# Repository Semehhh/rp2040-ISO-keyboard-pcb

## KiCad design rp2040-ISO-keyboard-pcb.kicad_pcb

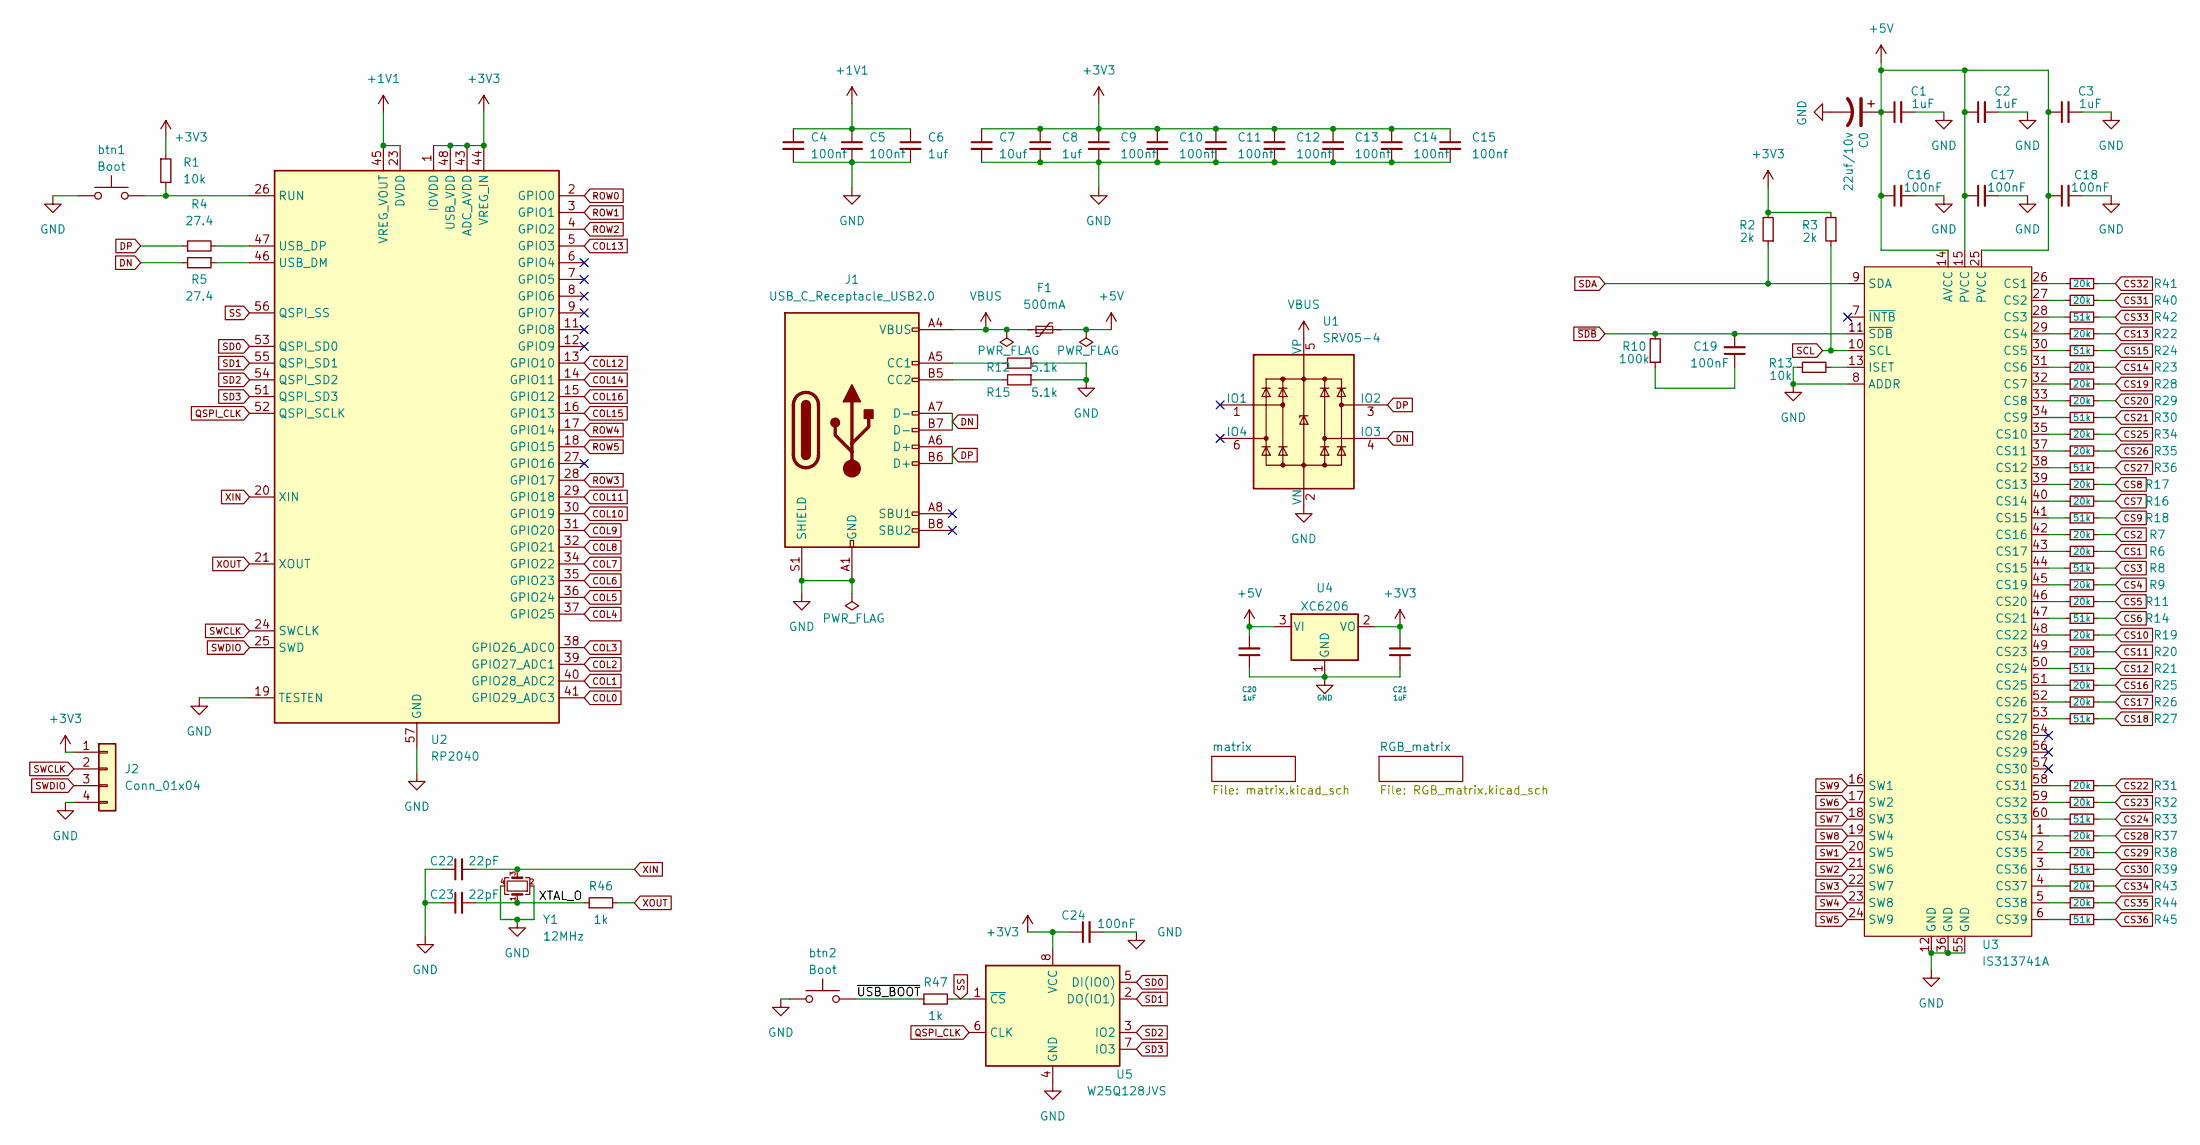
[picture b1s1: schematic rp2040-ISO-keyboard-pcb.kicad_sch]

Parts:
C0: 22uf/10v; CP_EIA-3216-18_Kemet-A; Part Number TAJA226K010RNJ; LCSC C11366
C1, C2, C3: 1uF; C_0402_1005Metric; LCSC C1555
C4, C5, C9, C10, C11, C12, C13, C14, C15: 100nf; C_0402_1005Metric
C6, C8: 1uf; C_0402_1005Metric
C7: 10uf; C_0402_1005Metric
C16, C17, C18, C19: 100nF; C_0402_1005Metric; LCSC C1555
C20, C21: 1uF; C_0402_1005Metric; LCSC C52923
C22, C23: 22pF; C_0402_1005Metric; LCSC C1555
C24: 100nF; C_0402_1005Metric; LCSC C1525
F1: 500mA; Fuse_1206_3216Metric
J1: USB_C_Receptacle_USB2.0; USB_C_Receptacle_HRO_TYPE-C-31-M-14
J2: Conn_01x04; PinHeader_1x04_P2.54mm_Vertical
R1: 10k; R_0402_1005Metric; LCSC C25744
R2, R3: 2k; R_0402_1005Metric
R4, R5: 27.4; R_0603_1608Metric
R6, R7, R9, R11, R16, R17, R19, R20, R22, R23, R25, R26, R28, R29, R31, R32, R34, R35, R37, R38, R40, R41, R43, R44: 20k; R_0402_1005Metric
R8, R14, R18, R21, R24, R27, R30, R33, R36, R39, R42, R45: 51k; R_0402_1005Metric
R10: 100k; R_0402_1005Metric
R12, R15: 5.1k; R_0402_1005Metric
R13: 10k; R_0402_1005Metric
R46, R47: 1k; R_0402_1005Metric; LCSC C11702
U1: SRV05-4; SOT-23-6-routable
U2: RP2040; QFN-56-1EP_7x7mm_P0.4mm_EP3.2x3.2mm
U3: IS313741A; QFN-60_EP_7x7_Pitch0.4mm
U4: XC6206; SOT-23; LCSC C5446
U5: W25Q128JVS; SOIC-8_5.23x5.23mm_P1.27mm; LCSC C97521
Y1: 12MHz; Crystal_SMD_3225-4Pin_3.2x2.5mm; LCSC C9002
btn1, btn2: Boot; PinSocket_1x02_P2.54mm_Vertical

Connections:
+1V1: C4.1, C5.1, C6.1, U2.23 (DVDD), U2.45 (VREG_VOUT), U2.50 (DVDD)
+3V3: C7.1, C8.1, C9.1, C10.1, C11.1, C12.1, C13.1, C14.1, C15.1, C21.2, C24.1, J2.1, R1.1, R2.2, R3.2, U2.1 (IOVDD), U2.10 (IOVDD), U2.22 (IOVDD), U2.33 (IOVDD), U2.42 (IOVDD), U2.43 (ADC_AVDD), U2.44 (VREG_IN), U2.48 (USB_VDD), U2.49 (IOVDD), U4.2 (VO), U5.8 (VCC)
+5V: C0.1, C1.1, C2.1, C3.1, C16.1, C17.1, C18.1, C20.2, F1.2, U3.14 (AVCC), U3.15 (PVCC), U3.25 (PVCC), U4.3 (VI)
/XTAL_O: C23.2, R46.1, Y1.1
/~USB_BOOT: R47.1, btn2.2
COL0: U2.41 (GPIO29_ADC3); also elsewhere on the board
COL1: U2.40 (GPIO28_ADC2); also elsewhere on the board
COL2: U2.39 (GPIO27_ADC1); also elsewhere on the board
COL3: U2.38 (GPIO26_ADC0); also elsewhere on the board
COL4: U2.37 (GPIO25); also elsewhere on the board
COL5: U2.36 (GPIO24); also elsewhere on the board
COL6: U2.35 (GPIO23); also elsewhere on the board
COL7: U2.34 (GPIO22); also elsewhere on the board
COL8: U2.32 (GPIO21); also elsewhere on the board
COL9: U2.31 (GPIO20); also elsewhere on the board
COL10: U2.30 (GPIO19); also elsewhere on the board
COL11: U2.29 (GPIO18); also elsewhere on the board
COL12: U2.13 (GPIO10); also elsewhere on the board
COL13: U2.5 (GPIO3); also elsewhere on the board
COL14: U2.14 (GPIO11); also elsewhere on the board
COL15: U2.16 (GPIO13); also elsewhere on the board
COL16: U2.15 (GPIO12); also elsewhere on the board
CS1: R6.2; also elsewhere on the board
CS2: R7.2; also elsewhere on the board
CS3: R8.2; also elsewhere on the board
CS4: R9.2; also elsewhere on the board
CS5: R11.2; also elsewhere on the board
CS6: R14.2; also elsewhere on the board
CS7: R16.2; also elsewhere on the board
CS8: R17.2; also elsewhere on the board
CS9: R18.2; also elsewhere on the board
CS10: R19.2; also elsewhere on the board
CS11: R20.2; also elsewhere on the board
CS12: R21.2; also elsewhere on the board
CS13: R22.2; also elsewhere on the board
CS14: R23.2; also elsewhere on the board
CS15: R24.2; also elsewhere on the board
CS16: R25.2; also elsewhere on the board
CS17: R26.2; also elsewhere on the board
CS18: R27.2; also elsewhere on the board
CS19: R28.2; also elsewhere on the board
CS20: R29.2; also elsewhere on the board
CS21: R30.2; also elsewhere on the board
CS22: R31.2; also elsewhere on the board
CS23: R32.2; also elsewhere on the board
CS24: R33.2; also elsewhere on the board
CS25: R34.2; also elsewhere on the board
CS26: R35.2; also elsewhere on the board
CS27: R36.2; also elsewhere on the board
CS28: R37.2; also elsewhere on the board
CS29: R38.2; also elsewhere on the board
CS30: R39.2; also elsewhere on the board
CS31: R40.2; also elsewhere on the board
CS32: R41.2; also elsewhere on the board
CS33: R42.2; also elsewhere on the board
CS34: R43.2; also elsewhere on the board
CS35: R44.2; also elsewhere on the board
CS36: R45.2; also elsewhere on the board
DN: J1.A7 (D-), J1.B7 (D-), R5.2, U1.4 (IO3)
DP: J1.A6 (D+), J1.B6 (D+), R4.1, U1.3 (IO2)
GND: C0.2, C1.2, C2.2, C3.2, C4.2, C5.2, C6.2, C7.2, C8.2, C9.2, C10.2, C11.2, C12.2, C13.2, C14.2, C15.2, C16.2, C17.2, C18.2, C20.1, C21.1, C22.1, C23.1, C24.2, J1.A1 (GND), J1.A12 (GND), J1.B1 (GND), J1.B12 (GND), J1.S1 (SHIELD), J2.4, R12.2, R13.1, R15.1, U1.2 (VN), U2.19 (TESTEN), U2.57 (GND), U3.8 (ADDR), U3.12 (GND), U3.36 (GND), U3.55 (GND), U3.61 (GND), U4.1 (GND), U5.4 (GND), Y1.2, Y1.4, btn1.1, btn2.1
unnamed: C19.1, R10.1
unnamed: J1.A5 (CC1), R12.1
unnamed: J1.B5 (CC2), R15.2
unnamed: R1.2, U2.26 (RUN), btn1.2
unnamed: R4.2, U2.47 (USB_DP)
unnamed: R5.1, U2.46 (USB_DM)
unnamed: R6.1, U3.43 (CS17)
unnamed: R7.1, U3.42 (CS16)
unnamed: R8.1, U3.44 (CS15)
unnamed: R9.1, U3.45 (CS19)
unnamed: R13.2, U3.13 (ISET)
unnamed: R16.1, U3.40 (CS14)
unnamed: R17.1, U3.39 (CS13)
unnamed: R18.1, U3.41 (CS15)
unnamed: R19.1, U3.48 (CS22)
unnamed: R20.1, U3.49 (CS23)
unnamed: R21.1, U3.50 (CS24)
unnamed: R22.1, U3.29 (CS4)
unnamed: R23.1, U3.31 (CS6)
unnamed: R24.1, U3.30 (CS5)
unnamed: R25.1, U3.51 (CS25)
unnamed: R26.1, U3.52 (CS26)
unnamed: R27.1, U3.53 (CS27)
unnamed: R28.1, U3.32 (CS7)
unnamed: R29.1, U3.33 (CS8)
unnamed: R30.1, U3.34 (CS9)
unnamed: R31.1, U3.58 (CS31)
unnamed: R32.1, U3.59 (CS32)
unnamed: R33.1, U3.60 (CS33)
unnamed: R34.1, U3.35 (CS10)
unnamed: R35.1, U3.37 (CS11)
unnamed: R36.1, U3.38 (CS12)
unnamed: R37.1, U3.1 (CS34)
unnamed: R38.1, U3.2 (CS35)
unnamed: R39.1, U3.3 (CS36)
unnamed: R40.1, U3.27 (CS2)
unnamed: R41.1, U3.26 (CS1)
unnamed: R42.1, U3.28 (CS3)
unnamed: R43.1, U3.4 (CS37)
unnamed: R44.1, U3.5 (CS38)
unnamed: R45.1, U3.6 (CS39)
unnamed: R11.1, U3.46 (CS20)
unnamed: R14.1, U3.47 (CS21)
QSPI_CLK: U2.52 (QSPI_SCLK), U5.6 (CLK)
ROW0: U2.2 (GPIO0); also elsewhere on the board
ROW1: U2.3 (GPIO1); also elsewhere on the board
ROW2: U2.4 (GPIO2); also elsewhere on the board
ROW3: U2.28 (GPIO17); also elsewhere on the board
ROW4: U2.17 (GPIO14); also elsewhere on the board
ROW5: U2.18 (GPIO15); also elsewhere on the board
SCL: R3.1, U3.10 (SCL)
SD0: U2.53 (QSPI_SD0), U5.5 (DI(IO0))
SD1: U2.55 (QSPI_SD1), U5.2 (DO(IO1))
SD2: U2.54 (QSPI_SD2), U5.3 (IO2)
SD3: U2.51 (QSPI_SD3), U5.7 (IO3)
SDA: R2.1, U3.9 (SDA)
SS: R47.2, U2.56 (QSPI_SS), U5.1 (~CS)
SW1: U3.20 (SW5); also elsewhere on the board
SW2: U3.21 (SW6); also elsewhere on the board
SW3: U3.22 (SW7); also elsewhere on the board
SW4: U3.23 (SW8); also elsewhere on the board
SW5: U3.24 (SW9); also elsewhere on the board
SW6: U3.17 (SW2); also elsewhere on the board
SW7: U3.18 (SW3); also elsewhere on the board
SW8: U3.19 (SW4); also elsewhere on the board
SW9: U3.16 (SW1); also elsewhere on the board
SWCLK: J2.2, U2.24 (SWCLK)
SWDIO: J2.3, U2.25 (SWD)
VBUS: F1.1, J1.A4 (VBUS), J1.A9 (VBUS), J1.B4 (VBUS), J1.B9 (VBUS), U1.5 (VP)
XIN: C22.2, U2.20 (XIN), Y1.3
XOUT: R46.2, U2.21 (XOUT)
~SDB: C19.2, R10.2, U3.11 (~SDB)

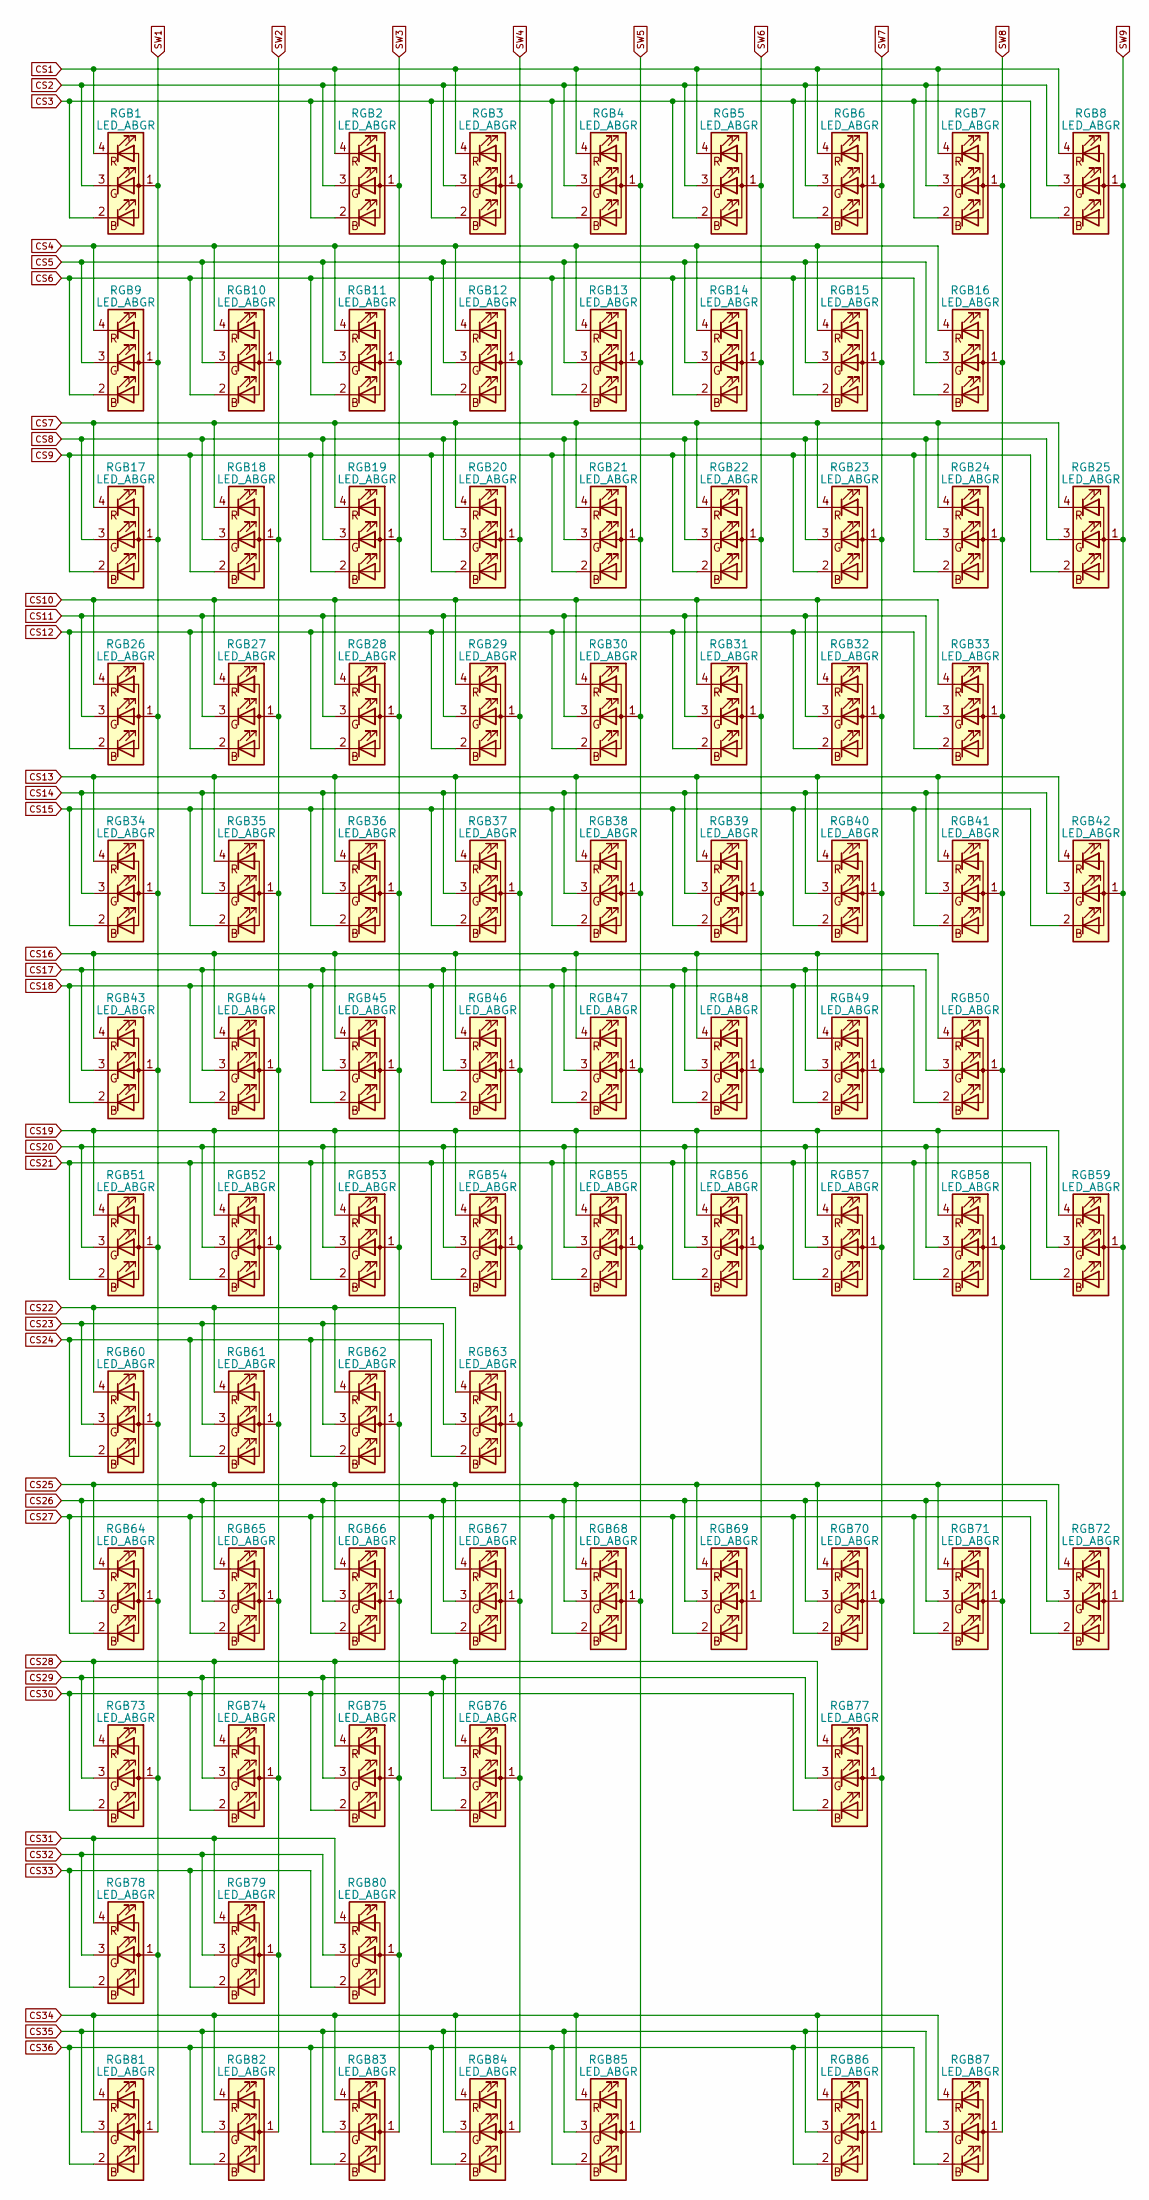
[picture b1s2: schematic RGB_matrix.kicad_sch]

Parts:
RGB1, RGB2, RGB3, RGB4, RGB5, RGB6, RGB7, RGB8, RGB9, RGB10, RGB11, RGB12, RGB13, RGB14, RGB15, RGB16, RGB17, RGB18, RGB19, RGB20, RGB21, RGB22, RGB23, RGB24, RGB25, RGB26, RGB27, RGB28, RGB29, RGB30, RGB31, RGB32, RGB33, RGB34, RGB35, RGB36, RGB37, RGB38, RGB39, RGB40, RGB41, RGB42, RGB43, RGB44, RGB45, RGB46, RGB47, RGB48, RGB49, RGB50, RGB51, RGB52, RGB53, RGB54, RGB55, RGB56, RGB57, RGB58, RGB59, RGB60, RGB61, RGB62, RGB63, RGB64, RGB65, RGB66, RGB67, RGB68, RGB69, RGB70, RGB71, RGB72, RGB73, RGB74, RGB75, RGB76, RGB77, RGB78, RGB79, RGB80, RGB81, RGB82, RGB83, RGB84, RGB85, RGB86, RGB87: LED_ABGR; MHT151RGBCT-RGB-Reverse-Mount-1206

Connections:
CS1: RGB1.4 (RK), RGB2.4 (RK), RGB3.4 (RK), RGB4.4 (RK), RGB5.4 (RK), RGB6.4 (RK), RGB7.4 (RK), RGB8.4 (RK); also elsewhere on the board
CS2: RGB1.3 (GK), RGB2.3 (GK), RGB3.3 (GK), RGB4.3 (GK), RGB5.3 (GK), RGB6.3 (GK), RGB7.3 (GK), RGB8.3 (GK); also elsewhere on the board
CS3: RGB1.2 (BK), RGB2.2 (BK), RGB3.2 (BK), RGB4.2 (BK), RGB5.2 (BK), RGB6.2 (BK), RGB7.2 (BK), RGB8.2 (BK); also elsewhere on the board
CS4: RGB9.4 (RK), RGB10.4 (RK), RGB11.4 (RK), RGB12.4 (RK), RGB13.4 (RK), RGB14.4 (RK), RGB15.4 (RK), RGB16.4 (RK); also elsewhere on the board
CS5: RGB9.3 (GK), RGB10.3 (GK), RGB11.3 (GK), RGB12.3 (GK), RGB13.3 (GK), RGB14.3 (GK), RGB15.3 (GK), RGB16.3 (GK); also elsewhere on the board
CS6: RGB9.2 (BK), RGB10.2 (BK), RGB11.2 (BK), RGB12.2 (BK), RGB13.2 (BK), RGB14.2 (BK), RGB15.2 (BK), RGB16.2 (BK); also elsewhere on the board
CS7: RGB17.4 (RK), RGB18.4 (RK), RGB19.4 (RK), RGB20.4 (RK), RGB21.4 (RK), RGB22.4 (RK), RGB23.4 (RK), RGB24.4 (RK), RGB25.4 (RK); also elsewhere on the board
CS8: RGB17.3 (GK), RGB18.3 (GK), RGB19.3 (GK), RGB20.3 (GK), RGB21.3 (GK), RGB22.3 (GK), RGB23.3 (GK), RGB24.3 (GK), RGB25.3 (GK); also elsewhere on the board
CS9: RGB17.2 (BK), RGB18.2 (BK), RGB19.2 (BK), RGB20.2 (BK), RGB21.2 (BK), RGB22.2 (BK), RGB23.2 (BK), RGB24.2 (BK), RGB25.2 (BK); also elsewhere on the board
CS10: RGB26.4 (RK), RGB27.4 (RK), RGB28.4 (RK), RGB29.4 (RK), RGB30.4 (RK), RGB31.4 (RK), RGB32.4 (RK), RGB33.4 (RK); also elsewhere on the board
CS11: RGB26.3 (GK), RGB27.3 (GK), RGB28.3 (GK), RGB29.3 (GK), RGB30.3 (GK), RGB31.3 (GK), RGB32.3 (GK), RGB33.3 (GK); also elsewhere on the board
CS12: RGB26.2 (BK), RGB27.2 (BK), RGB28.2 (BK), RGB29.2 (BK), RGB30.2 (BK), RGB31.2 (BK), RGB32.2 (BK), RGB33.2 (BK); also elsewhere on the board
CS13: RGB34.4 (RK), RGB35.4 (RK), RGB36.4 (RK), RGB37.4 (RK), RGB38.4 (RK), RGB39.4 (RK), RGB40.4 (RK), RGB41.4 (RK), RGB42.4 (RK); also elsewhere on the board
CS14: RGB34.3 (GK), RGB35.3 (GK), RGB36.3 (GK), RGB37.3 (GK), RGB38.3 (GK), RGB39.3 (GK), RGB40.3 (GK), RGB41.3 (GK), RGB42.3 (GK); also elsewhere on the board
CS15: RGB34.2 (BK), RGB35.2 (BK), RGB36.2 (BK), RGB37.2 (BK), RGB38.2 (BK), RGB39.2 (BK), RGB40.2 (BK), RGB41.2 (BK), RGB42.2 (BK); also elsewhere on the board
CS16: RGB43.4 (RK), RGB44.4 (RK), RGB45.4 (RK), RGB46.4 (RK), RGB47.4 (RK), RGB48.4 (RK), RGB49.4 (RK), RGB50.4 (RK); also elsewhere on the board
CS17: RGB43.3 (GK), RGB44.3 (GK), RGB45.3 (GK), RGB46.3 (GK), RGB47.3 (GK), RGB48.3 (GK), RGB49.3 (GK), RGB50.3 (GK); also elsewhere on the board
CS18: RGB43.2 (BK), RGB44.2 (BK), RGB45.2 (BK), RGB46.2 (BK), RGB47.2 (BK), RGB48.2 (BK), RGB49.2 (BK), RGB50.2 (BK); also elsewhere on the board
CS19: RGB51.4 (RK), RGB52.4 (RK), RGB53.4 (RK), RGB54.4 (RK), RGB55.4 (RK), RGB56.4 (RK), RGB57.4 (RK), RGB58.4 (RK), RGB59.4 (RK); also elsewhere on the board
CS20: RGB51.3 (GK), RGB52.3 (GK), RGB53.3 (GK), RGB54.3 (GK), RGB55.3 (GK), RGB56.3 (GK), RGB57.3 (GK), RGB58.3 (GK), RGB59.3 (GK); also elsewhere on the board
CS21: RGB51.2 (BK), RGB52.2 (BK), RGB53.2 (BK), RGB54.2 (BK), RGB55.2 (BK), RGB56.2 (BK), RGB57.2 (BK), RGB58.2 (BK), RGB59.2 (BK); also elsewhere on the board
CS22: RGB60.4 (RK), RGB61.4 (RK), RGB62.4 (RK), RGB63.4 (RK); also elsewhere on the board
CS23: RGB60.3 (GK), RGB61.3 (GK), RGB62.3 (GK), RGB63.3 (GK); also elsewhere on the board
CS24: RGB60.2 (BK), RGB61.2 (BK), RGB62.2 (BK), RGB63.2 (BK); also elsewhere on the board
CS25: RGB64.4 (RK), RGB65.4 (RK), RGB66.4 (RK), RGB67.4 (RK), RGB68.4 (RK), RGB69.4 (RK), RGB70.4 (RK), RGB71.4 (RK), RGB72.4 (RK); also elsewhere on the board
CS26: RGB64.3 (GK), RGB65.3 (GK), RGB66.3 (GK), RGB67.3 (GK), RGB68.3 (GK), RGB69.3 (GK), RGB70.3 (GK), RGB71.3 (GK), RGB72.3 (GK); also elsewhere on the board
CS27: RGB64.2 (BK), RGB65.2 (BK), RGB66.2 (BK), RGB67.2 (BK), RGB68.2 (BK), RGB69.2 (BK), RGB70.2 (BK), RGB71.2 (BK), RGB72.2 (BK); also elsewhere on the board
CS28: RGB73.4 (RK), RGB74.4 (RK), RGB75.4 (RK), RGB76.4 (RK), RGB77.4 (RK); also elsewhere on the board
CS29: RGB73.3 (GK), RGB74.3 (GK), RGB75.3 (GK), RGB76.3 (GK), RGB77.3 (GK); also elsewhere on the board
CS30: RGB73.2 (BK), RGB74.2 (BK), RGB75.2 (BK), RGB76.2 (BK), RGB77.2 (BK); also elsewhere on the board
CS31: RGB78.4 (RK), RGB79.4 (RK), RGB80.4 (RK); also elsewhere on the board
CS32: RGB78.3 (GK), RGB79.3 (GK), RGB80.3 (GK); also elsewhere on the board
CS33: RGB78.2 (BK), RGB79.2 (BK), RGB80.2 (BK); also elsewhere on the board
CS34: RGB81.4 (RK), RGB82.4 (RK), RGB83.4 (RK), RGB84.4 (RK), RGB85.4 (RK), RGB86.4 (RK), RGB87.4 (RK); also elsewhere on the board
CS35: RGB81.3 (GK), RGB82.3 (GK), RGB83.3 (GK), RGB84.3 (GK), RGB85.3 (GK), RGB86.3 (GK), RGB87.3 (GK); also elsewhere on the board
CS36: RGB81.2 (BK), RGB82.2 (BK), RGB83.2 (BK), RGB84.2 (BK), RGB85.2 (BK), RGB86.2 (BK), RGB87.2 (BK); also elsewhere on the board
SW1: RGB1.1 (A), RGB9.1 (A), RGB17.1 (A), RGB26.1 (A), RGB34.1 (A), RGB43.1 (A), RGB51.1 (A), RGB60.1 (A), RGB64.1 (A), RGB73.1 (A), RGB78.1 (A), RGB81.1 (A); also elsewhere on the board
SW2: RGB10.1 (A), RGB18.1 (A), RGB27.1 (A), RGB35.1 (A), RGB44.1 (A), RGB52.1 (A), RGB61.1 (A), RGB65.1 (A), RGB74.1 (A), RGB79.1 (A), RGB82.1 (A); also elsewhere on the board
SW3: RGB2.1 (A), RGB11.1 (A), RGB19.1 (A), RGB28.1 (A), RGB36.1 (A), RGB45.1 (A), RGB53.1 (A), RGB62.1 (A), RGB66.1 (A), RGB75.1 (A), RGB80.1 (A), RGB83.1 (A); also elsewhere on the board
SW4: RGB3.1 (A), RGB12.1 (A), RGB20.1 (A), RGB29.1 (A), RGB37.1 (A), RGB46.1 (A), RGB54.1 (A), RGB63.1 (A), RGB67.1 (A), RGB76.1 (A), RGB84.1 (A); also elsewhere on the board
SW5: RGB4.1 (A), RGB13.1 (A), RGB21.1 (A), RGB30.1 (A), RGB38.1 (A), RGB47.1 (A), RGB55.1 (A), RGB68.1 (A), RGB85.1 (A); also elsewhere on the board
SW6: RGB5.1 (A), RGB14.1 (A), RGB22.1 (A), RGB31.1 (A), RGB39.1 (A), RGB48.1 (A), RGB56.1 (A), RGB69.1 (A); also elsewhere on the board
SW7: RGB6.1 (A), RGB15.1 (A), RGB23.1 (A), RGB32.1 (A), RGB40.1 (A), RGB49.1 (A), RGB57.1 (A), RGB70.1 (A), RGB77.1 (A), RGB86.1 (A); also elsewhere on the board
SW8: RGB7.1 (A), RGB16.1 (A), RGB24.1 (A), RGB33.1 (A), RGB41.1 (A), RGB50.1 (A), RGB58.1 (A), RGB71.1 (A), RGB87.1 (A); also elsewhere on the board
SW9: RGB8.1 (A), RGB25.1 (A), RGB42.1 (A), RGB59.1 (A), RGB72.1 (A); also elsewhere on the board

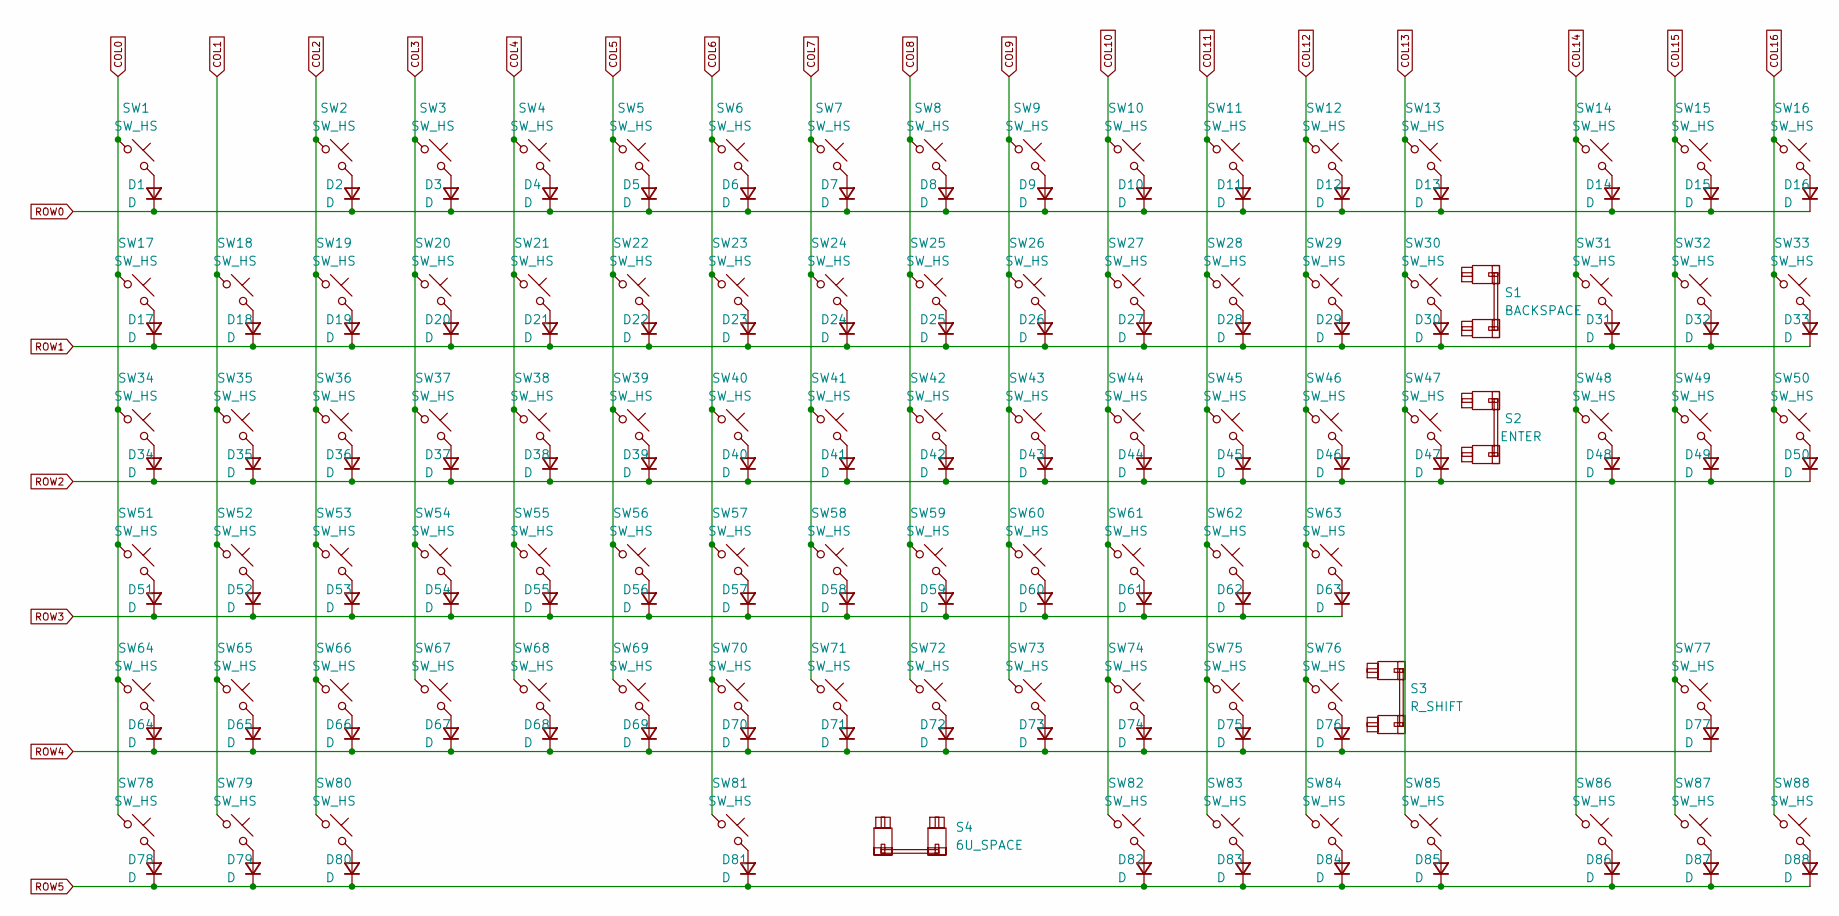
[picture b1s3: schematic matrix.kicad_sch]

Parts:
D1, D2, D3, D4, D5, D6, D7, D8, D9, D10, D11, D12, D13, D14, D15, D16, D17, D18, D19, D20, D21, D22, D23, D24, D25, D26, D27, D28, D29, D30, D31, D32, D33, D34, D35, D36, D37, D38, D39, D40, D41, D42, D43, D44, D45, D46, D47, D48, D49, D50, D51, D52, D53, D54, D55, D56, D57, D58, D59, D60, D61, D62, D63, D64, D65, D66, D67, D68, D69, D70, D71, D72, D73, D74, D75, D76, D77, D78, D79, D80, D81, D82, D83, D84, D85, D86, D87, D88: D; D_SOD-123
S1: BACKSPACE; STAB_MX_2u
S2: ENTER; STAB_MX_ISO_FLIPPED
S3: R_SHIFT; STAB_MX_2.75u
S4: 6U_SPACE; STAB_MX_6u
SW1, SW2, SW3, SW4, SW5, SW6, SW7, SW8, SW9, SW10, SW11, SW12, SW13, SW14, SW15, SW16, SW17, SW18, SW19, SW20, SW21, SW22, SW23, SW24, SW25, SW26, SW27, SW28, SW29, SW30, SW31, SW32, SW33, SW35, SW36, SW37, SW38, SW39, SW40, SW41, SW42, SW43, SW44, SW45, SW46, SW47, SW48, SW49, SW50, SW52, SW53, SW54, SW55, SW56, SW57, SW58, SW59, SW60, SW61, SW62, SW63, SW65, SW66, SW67, SW68, SW69, SW70, SW71, SW72, SW73, SW74, SW75, SW76, SW77, SW79, SW81, SW83, SW84, SW86, SW87, SW88: SW_HS; SW_MX_HS_1u
SW34, SW78, SW80, SW82, SW85: SW_HS; SW_MX_HS_1.5u
SW51: SW_HS; SW_MX_HS_1.75u
SW64: SW_HS; SW_MX_HS_1.25u

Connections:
COL0: SW1.1, SW17.1, SW34.1, SW51.1, SW64.1, SW78.1; also elsewhere on the board
COL1: SW18.1, SW35.1, SW52.1, SW65.1, SW79.1; also elsewhere on the board
COL2: SW2.1, SW19.1, SW36.1, SW53.1, SW66.1, SW80.1; also elsewhere on the board
COL3: SW3.1, SW20.1, SW37.1, SW54.1, SW67.1; also elsewhere on the board
COL4: SW4.1, SW21.1, SW38.1, SW55.1, SW68.1; also elsewhere on the board
COL5: SW5.1, SW22.1, SW39.1, SW56.1, SW69.1; also elsewhere on the board
COL6: SW6.1, SW23.1, SW40.1, SW57.1, SW70.1, SW81.1; also elsewhere on the board
COL7: SW7.1, SW24.1, SW41.1, SW58.1, SW71.1; also elsewhere on the board
COL8: SW8.1, SW25.1, SW42.1, SW59.1, SW72.1; also elsewhere on the board
COL9: SW9.1, SW26.1, SW43.1, SW60.1, SW73.1; also elsewhere on the board
COL10: SW10.1, SW27.1, SW44.1, SW61.1, SW74.1, SW82.1; also elsewhere on the board
COL11: SW11.1, SW28.1, SW45.1, SW62.1, SW75.1, SW83.1; also elsewhere on the board
COL12: SW12.1, SW29.1, SW46.1, SW63.1, SW76.1, SW84.1; also elsewhere on the board
COL13: SW13.1, SW30.1, SW47.1, SW85.1; also elsewhere on the board
COL14: SW14.1, SW31.1, SW48.1, SW86.1; also elsewhere on the board
COL15: SW15.1, SW32.1, SW49.1, SW77.1, SW87.1; also elsewhere on the board
COL16: SW16.1, SW33.1, SW50.1, SW88.1; also elsewhere on the board
unnamed: D1.2 (A), SW1.2
unnamed: D2.2 (A), SW2.2
unnamed: D3.2 (A), SW3.2
unnamed: D4.2 (A), SW4.2
unnamed: D5.2 (A), SW5.2
unnamed: D6.2 (A), SW6.2
unnamed: D7.2 (A), SW7.2
unnamed: D8.2 (A), SW8.2
unnamed: D9.2 (A), SW9.2
unnamed: D10.2 (A), SW10.2
unnamed: D11.2 (A), SW11.2
unnamed: D12.2 (A), SW12.2
unnamed: D13.2 (A), SW13.2
unnamed: D14.2 (A), SW14.2
unnamed: D15.2 (A), SW15.2
unnamed: D16.2 (A), SW16.2
unnamed: D17.2 (A), SW17.2
unnamed: D18.2 (A), SW18.2
unnamed: D19.2 (A), SW19.2
unnamed: D20.2 (A), SW20.2
unnamed: D21.2 (A), SW21.2
unnamed: D22.2 (A), SW22.2
unnamed: D23.2 (A), SW23.2
unnamed: D24.2 (A), SW24.2
unnamed: D25.2 (A), SW25.2
unnamed: D26.2 (A), SW26.2
unnamed: D27.2 (A), SW27.2
unnamed: D28.2 (A), SW28.2
unnamed: D29.2 (A), SW29.2
unnamed: D30.2 (A), SW30.2
unnamed: D31.2 (A), SW31.2
unnamed: D32.2 (A), SW32.2
unnamed: D33.2 (A), SW33.2
unnamed: D34.2 (A), SW34.2
unnamed: D35.2 (A), SW35.2
unnamed: D36.2 (A), SW36.2
unnamed: D37.2 (A), SW37.2
unnamed: D38.2 (A), SW38.2
unnamed: D39.2 (A), SW39.2
unnamed: D40.2 (A), SW40.2
unnamed: D41.2 (A), SW41.2
unnamed: D42.2 (A), SW42.2
unnamed: D43.2 (A), SW43.2
unnamed: D44.2 (A), SW44.2
unnamed: D45.2 (A), SW45.2
unnamed: D46.2 (A), SW46.2
unnamed: D47.2 (A), SW47.2
unnamed: D48.2 (A), SW48.2
unnamed: D49.2 (A), SW49.2
unnamed: D50.2 (A), SW50.2
unnamed: D51.2 (A), SW51.2
unnamed: D52.2 (A), SW52.2
unnamed: D53.2 (A), SW53.2
unnamed: D54.2 (A), SW54.2
unnamed: D55.2 (A), SW55.2
unnamed: D56.2 (A), SW56.2
unnamed: D57.2 (A), SW57.2
unnamed: D58.2 (A), SW58.2
unnamed: D59.2 (A), SW59.2
unnamed: D60.2 (A), SW60.2
unnamed: D61.2 (A), SW61.2
unnamed: D62.2 (A), SW62.2
unnamed: D63.2 (A), SW63.2
unnamed: D64.2 (A), SW64.2
unnamed: D65.2 (A), SW65.2
unnamed: D66.2 (A), SW66.2
unnamed: D67.2 (A), SW67.2
unnamed: D68.2 (A), SW68.2
unnamed: D69.2 (A), SW69.2
unnamed: D70.2 (A), SW70.2
unnamed: D71.2 (A), SW71.2
unnamed: D72.2 (A), SW72.2
unnamed: D73.2 (A), SW73.2
unnamed: D74.2 (A), SW74.2
unnamed: D75.2 (A), SW75.2
unnamed: D76.2 (A), SW76.2
unnamed: D77.2 (A), SW77.2
unnamed: D78.2 (A), SW78.2
unnamed: D79.2 (A), SW79.2
unnamed: D80.2 (A), SW80.2
unnamed: D81.2 (A), SW81.2
unnamed: D82.2 (A), SW82.2
unnamed: D83.2 (A), SW83.2
unnamed: D84.2 (A), SW84.2
unnamed: D85.2 (A), SW85.2
unnamed: D86.2 (A), SW86.2
unnamed: D87.2 (A), SW87.2
unnamed: D88.2 (A), SW88.2
ROW0: D1.1 (K), D2.1 (K), D3.1 (K), D4.1 (K), D5.1 (K), D6.1 (K), D7.1 (K), D8.1 (K), D9.1 (K), D10.1 (K), D11.1 (K), D12.1 (K), D13.1 (K), D14.1 (K), D15.1 (K), D16.1 (K); also elsewhere on the board
ROW1: D17.1 (K), D18.1 (K), D19.1 (K), D20.1 (K), D21.1 (K), D22.1 (K), D23.1 (K), D24.1 (K), D25.1 (K), D26.1 (K), D27.1 (K), D28.1 (K), D29.1 (K), D30.1 (K), D31.1 (K), D32.1 (K), D33.1 (K); also elsewhere on the board
ROW2: D34.1 (K), D35.1 (K), D36.1 (K), D37.1 (K), D38.1 (K), D39.1 (K), D40.1 (K), D41.1 (K), D42.1 (K), D43.1 (K), D44.1 (K), D45.1 (K), D46.1 (K), D47.1 (K), D48.1 (K), D49.1 (K), D50.1 (K); also elsewhere on the board
ROW3: D51.1 (K), D52.1 (K), D53.1 (K), D54.1 (K), D55.1 (K), D56.1 (K), D57.1 (K), D58.1 (K), D59.1 (K), D60.1 (K), D61.1 (K), D62.1 (K), D63.1 (K); also elsewhere on the board
ROW4: D64.1 (K), D65.1 (K), D66.1 (K), D67.1 (K), D68.1 (K), D69.1 (K), D70.1 (K), D71.1 (K), D72.1 (K), D73.1 (K), D74.1 (K), D75.1 (K), D76.1 (K), D77.1 (K); also elsewhere on the board
ROW5: D78.1 (K), D79.1 (K), D80.1 (K), D81.1 (K), D82.1 (K), D83.1 (K), D84.1 (K), D85.1 (K), D86.1 (K), D87.1 (K), D88.1 (K); also elsewhere on the board

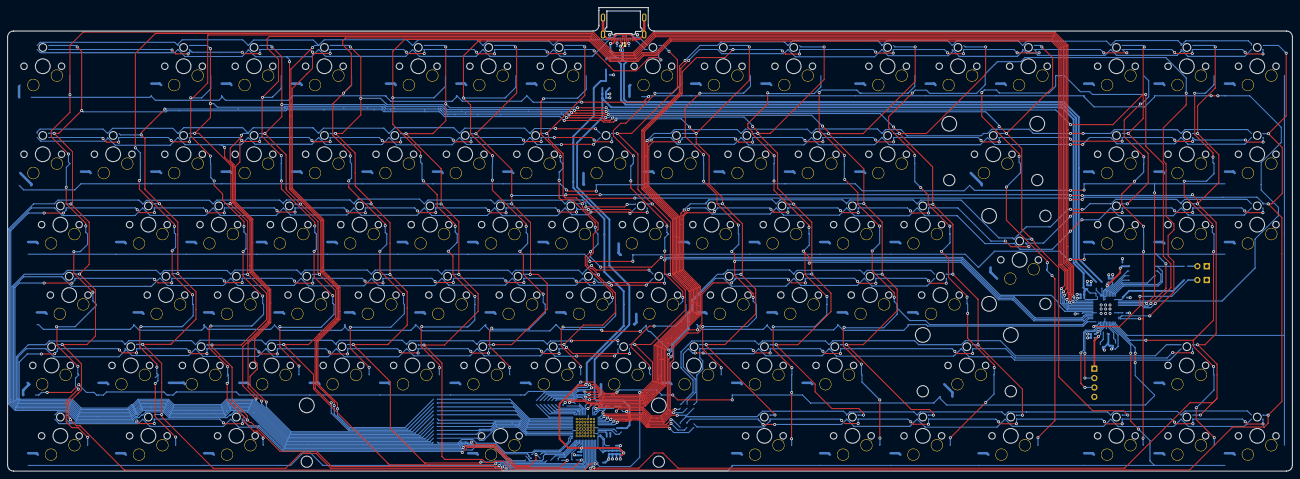
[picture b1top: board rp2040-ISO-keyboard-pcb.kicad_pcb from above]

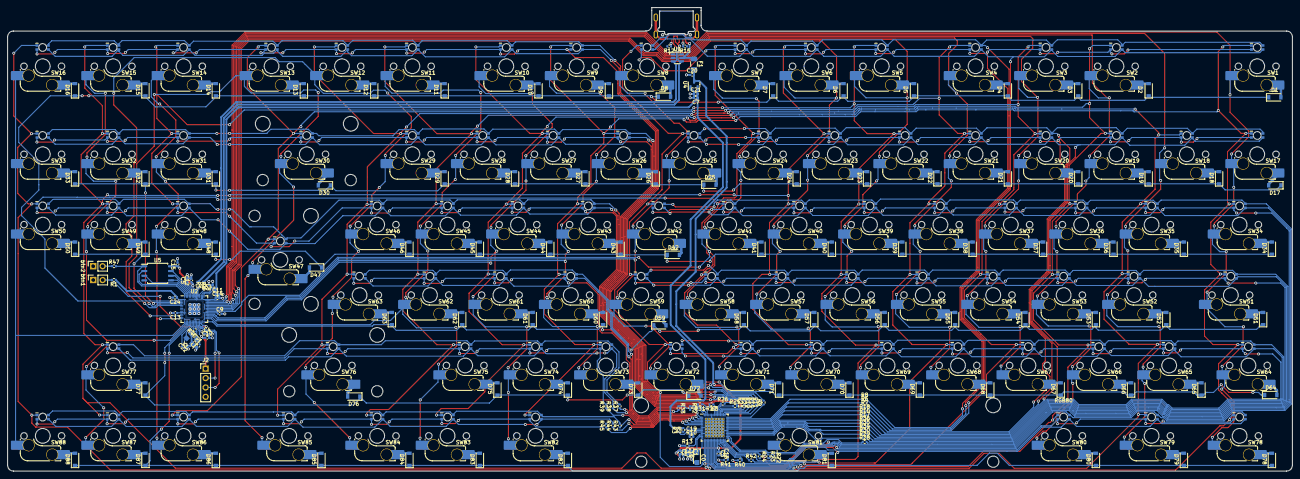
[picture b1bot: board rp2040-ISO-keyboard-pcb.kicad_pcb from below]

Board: 2 copper layers, 347.7 x 125.4 mm, 350 parts (345 on the bottom side), 221 nets.

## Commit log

2023-01-12 init
2023-01-12 added some components
2023-01-13 added keymatrix with stabs
2023-01-14 added capacitors for LEDs and annotatios
2023-01-14 added footprints to compontents
2023-01-17 loaded and fipped footprints to pcb editor
2023-01-17 placed switches and LEDs
2023-01-18 IS313741A added with some wires
2023-01-19 added sw and cs labels to led driver
2023-01-19 added rgb matrix
2023-01-21 some layouts done
2023-01-21 corrected top row layout
2023-01-24 improved rgb schematic
2023-01-24 small fixes
2023-01-25 wiring components
2023-01-25 more routing done
2023-01-26 sw pins done
2023-01-27 some more CS pins done
2023-01-27 more routing
2023-01-28 added more routing
2023-01-28 updated lib
2023-01-29 routing finished
2023-01-29 *now finished routing (zones left)
2023-01-30 cleaned up some routing and used smaller resistors (0402 instead of 0603)
2023-02-10 added ground layers
2023-02-10 grounding improved
2023-02-13 probably finished everything but design
